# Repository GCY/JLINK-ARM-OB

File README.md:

# JLINK-ARM-OB
This is JLink-OB ARM ICE tool, [STM32F103 Jan 7 2019 firmware](https://github.com/GCY/JLINK-ARM-OB/blob/master/J-Link%20OB-STM32F103%20V1%20compiled%20Jan%20%207%202019/JLink-OB%20STM32F103%20JLinkARM.dll%20v6.44f%20.bin) extract from v6.44 JLinkARM.dll.

This version([STM32F103 Jan 7 2019](https://github.com/GCY/JLINK-ARM-OB/blob/master/J-Link%20OB-STM32F103%20V1%20compiled%20Jan%20%207%202019/JLink-OB%20STM32F103%20JLinkARM.dll%20v6.44f%20.bin) ) failed to upgrade the firmware of the JLink-OB with JLinkConfig.

## Use
 - 1.burning [STM32F103 Jan 7 2019 firmware](https://github.com/GCY/JLINK-ARM-OB/blob/master/J-Link%20OB-STM32F103%20V1%20compiled%20Jan%20%207%202019/JLink-OB%20STM32F103%20JLinkARM.dll%20v6.44f%20.bin) to DIY JLink-OB.
 - 2.Connect targer(For example the following picture is my [STM32F405 Digital Stethoscope project](https://github.com/GCY/Digital-Stethoscope-for-Heart-and-Lung-sounds))

 - 1.Run JLinkExe.
 - 2.J-Link > connect.
 - 3.Select device.     # the example is STM32F405
 - 4.Device > S.        # for SWD Port
 - 5.Speed = 4000kHz

 - 1.J-Link > mem 0x8000000 40960
 - 2.Test dump target flash.
 - 3.You DIY JLink-OB done.

## Reference
 - [DIY JLink-OB-072 (JLink + COM)](http://akb77.com/g/stm32/jlink-ob/)
 - [JLink hack reference (cht)](https://www.amobbs.com/thread-5653964-1-1.html)
 - [J-Link Commander](https://wiki.segger.com/J-Link_Commander#savebin)
 - [Firmware extract from JLinkARM.dll (cht)](https://blog.csdn.net/qq_39663845/article/details/81086499)

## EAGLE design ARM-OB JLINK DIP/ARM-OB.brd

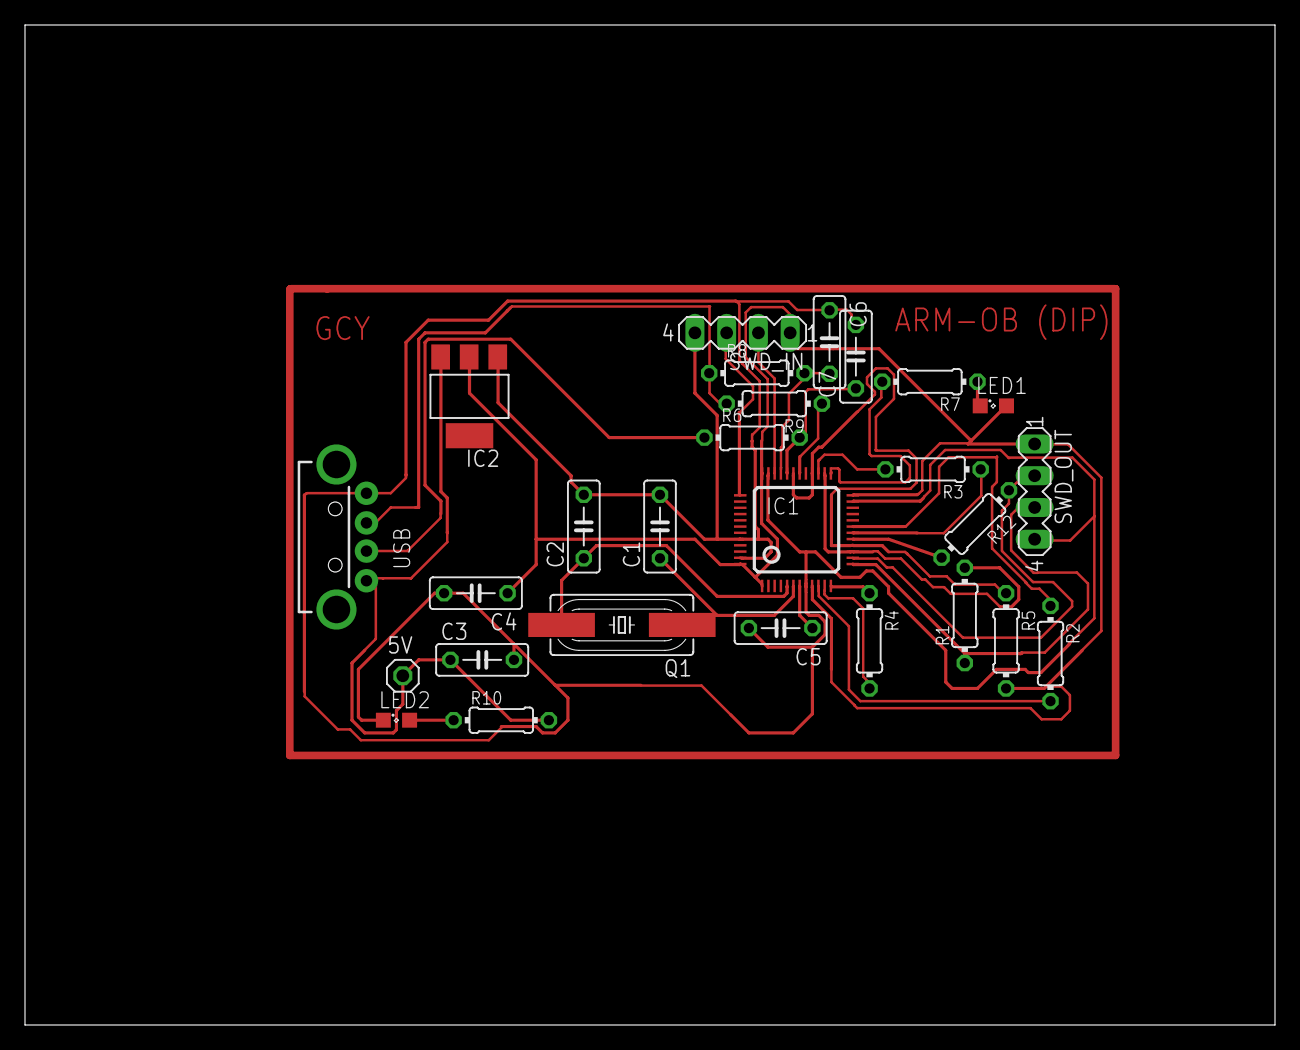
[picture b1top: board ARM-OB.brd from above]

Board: 2 copper layers, 100.0 x 80.0 mm, 28 parts (0 on the bottom side), 21 nets.

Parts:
5V: 1X01
C1, C2, C6, C7: 22pF; C050-025X075
C3, C4, C5: 0.1uF; C050-025X075
FRAME1: FRAME-LETTER; CREATIVE_COMMONS
IC1: STM32F10XCXT6; TQFP48
IC2: REG1117; SOT223
LED1, LED2: SML0805
Q1: 8MHz; HC49UP
R1, R2, R3, R4, R12: 100; 0204/7
R5: 10k; 0204/7
R6, R8: 68; 0204/7
R7, R10: 1k; 0204/7
R9: 1.5k; 0204/7
SWD_IN: MA04-1
SWD_OUT: MA04-1
USB: USB-A-H

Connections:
D-: IC1.32, R6.2
unnamed: C5.1, IC1.7
unnamed: C2.1, IC1.5, Q1.2
unnamed: C1.1, IC1.6, Q1.1
unnamed: LED2.A, R10.1
unnamed: LED1.C, R7.1
S$14: IC1.14, R12.1
S$30: C1.2, C2.2, IC1.44, IC1.47, IC2.1, SWD_IN.4
S$32: C5.2, IC1.8, IC1.35
S$34: LED1.A, SWD_OUT.1
S$38: IC1.28, IC1.31
S$47: C3.2, C4.2, LED2.C
SWDIO_IN: IC1.34, SWD_IN.2
TCK_I: IC1.13, R1.1
TCK_O: IC1.15, IC1.26
TDI_O: IC1.27, R3.2
TMS_O: IC1.17, R12.2
TRES_I: IC1.12, R4.1
TRST_O: IC1.10, R2.2
VCC: 5V.1, C3.1, R10.2
VDD: C4.1, IC1.1, IC1.36, IC1.48, IC2.2

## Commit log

2015-01-10 DIP Version
2018-04-24 photo
2020-06-10 J-Link OB-STM32F103 V1 compiled Jan 7 2019
2020-06-10 rename
2020-06-10 delete
2020-06-10 recovery
2020-07-14 add dump_firmware.c

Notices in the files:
parts and their libraries:
SparkFun-Connectors: Licensing: CC v3.0 Share-Alike You are welcome to use this library for commercial purposes.
SparkFun-Aesthetics: Released under the Creative Commons Attribution Share-Alike 3.0 License
SparkFun-Aesthetics: http://creativecommons.org/licenses/by-sa/3.0
